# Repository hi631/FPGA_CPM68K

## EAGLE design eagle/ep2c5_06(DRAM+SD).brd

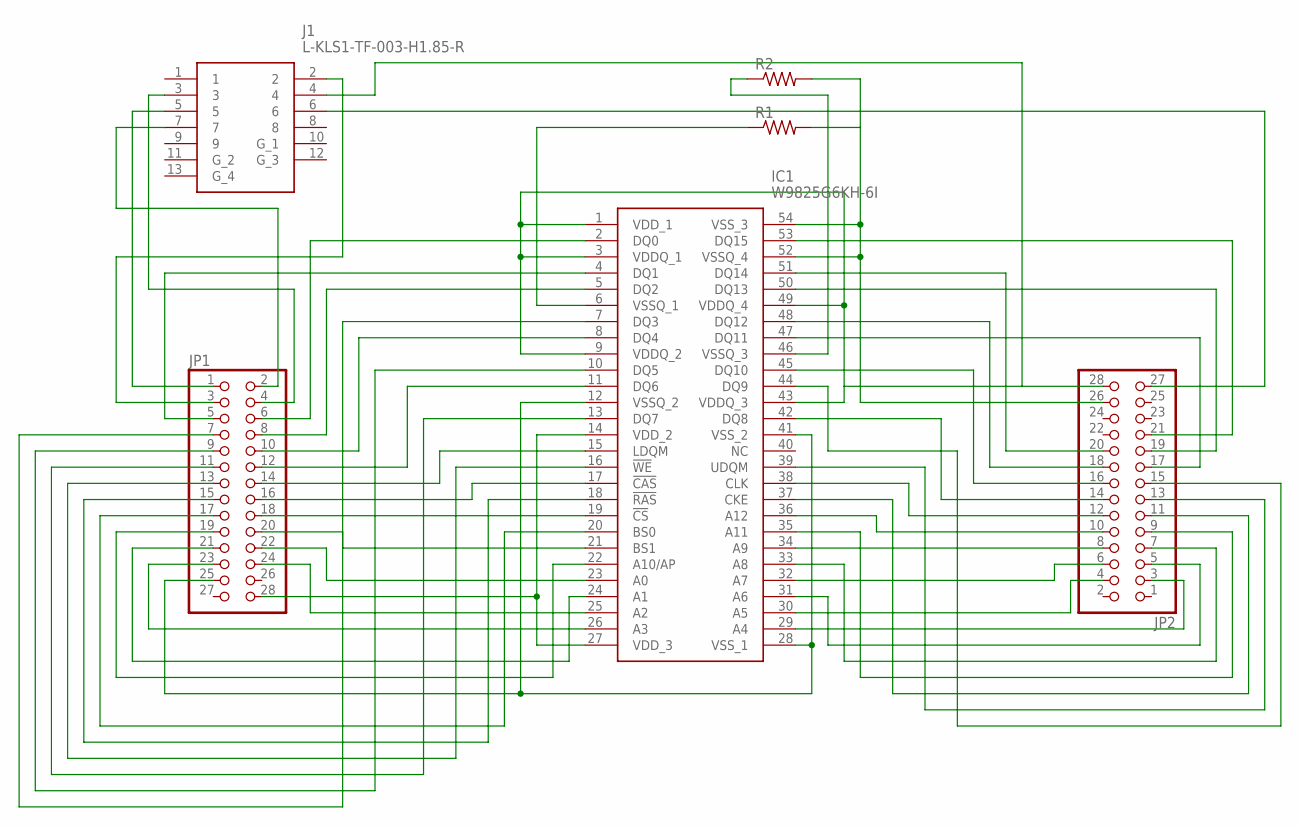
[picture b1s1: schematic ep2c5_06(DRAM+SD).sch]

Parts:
IC1: W9825G6KH-6I; SOP80P1176X120-54N
J1: L-KLS1-TF-003-H1.85-R
JP1, JP2: PINHD-2X14; 2X14
R1, R2: R-US_R0805; R0805

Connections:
unnamed: IC1.14 (VDD_2), IC1.27 (VDD_3), JP1.28
unnamed: IC1.12 (VSSQ_2), IC1.28 (VSS_1), IC1.41 (VSS_2), JP1.25
unnamed: IC1.1 (VDD_1), IC1.3 (VDDQ_1), IC1.9 (VDDQ_2), IC1.43 (VDDQ_3), IC1.49 (VDDQ_4), J1.4, JP2.28
unnamed: IC1.52 (VSSQ_4), IC1.54 (VSS_3), JP2.26, R1.2, R2.2
unnamed: IC1.6 (VSSQ_1), R1.1
unnamed: IC1.46 (VSSQ_3), R2.1
unnamed: IC1.26 (A3), JP1.23
unnamed: IC1.25 (A2), JP1.24
unnamed: IC1.24 (A1), JP1.21
unnamed: IC1.23 (A0), JP1.22
unnamed: IC1.22 (A10/AP), JP1.19
unnamed: IC1.21 (BS1), JP1.20
unnamed: IC1.20 (BS0), JP1.17
unnamed: IC1.19 (!CS), JP1.18
unnamed: IC1.18 (!RAS), JP1.15
unnamed: IC1.17 (!CAS), JP1.16
unnamed: IC1.16 (!WE), JP1.13
unnamed: IC1.15 (LDQM), JP1.14
unnamed: IC1.13 (DQ7), JP1.11
unnamed: IC1.11 (DQ6), JP1.12
unnamed: IC1.10 (DQ5), JP1.9
unnamed: IC1.8 (DQ4), JP1.10
unnamed: IC1.7 (DQ3), JP1.7
unnamed: IC1.5 (DQ2), JP1.8
unnamed: IC1.4 (DQ1), JP1.5
unnamed: IC1.2 (DQ0), JP1.6
unnamed: IC1.29 (A4), JP2.3
unnamed: IC1.30 (A5), JP2.4
unnamed: IC1.31 (A6), JP2.5
unnamed: IC1.32 (A7), JP2.6
unnamed: IC1.33 (A8), JP2.7
unnamed: IC1.34 (A9), JP2.8
unnamed: IC1.35 (A11), JP2.9
unnamed: IC1.36 (A12), JP2.10
unnamed: IC1.37 (CKE), JP2.11
unnamed: IC1.38 (CLK), JP2.12
unnamed: IC1.39 (UDQM), JP2.13
unnamed: IC1.42 (DQ8), JP2.14
unnamed: IC1.44 (DQ9), JP2.15
unnamed: IC1.45 (DQ10), JP2.16
unnamed: IC1.47 (DQ11), JP2.17
unnamed: IC1.48 (DQ12), JP2.18
unnamed: IC1.50 (DQ13), JP2.19
unnamed: IC1.51 (DQ14), JP2.20
unnamed: IC1.53 (DQ15), JP2.21
unnamed: J1.6, JP2.27
unnamed: J1.2, JP1.3
unnamed: J1.3, JP1.4
unnamed: J1.5, JP1.1
unnamed: J1.7, JP1.2

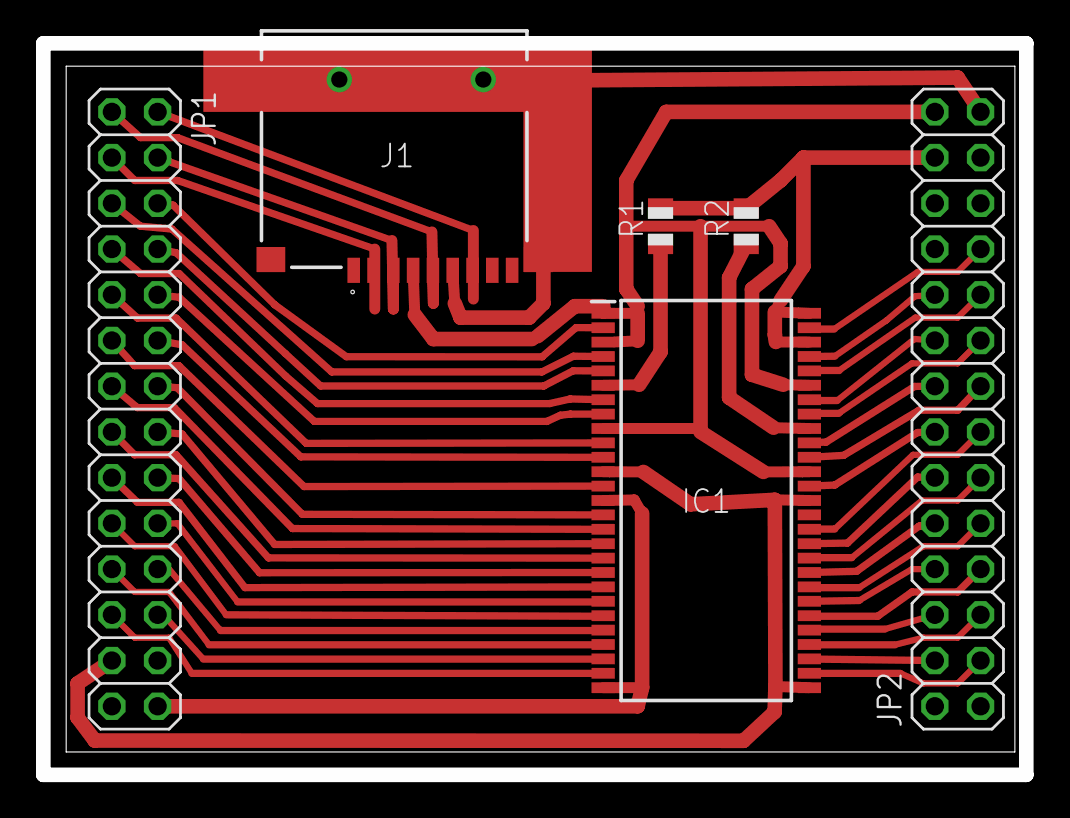
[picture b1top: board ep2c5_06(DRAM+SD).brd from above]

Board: 2 copper layers, 54.6 x 40.6 mm, 6 parts (0 on the bottom side), 50 nets.
